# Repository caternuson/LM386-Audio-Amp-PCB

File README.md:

# LM386 Audio Amp PCB
EAGLE files for simple LM386 single channel audio amp with adjustable gain. Also available at [OSH Park](https://oshpark.com/shared_projects/PH3KykbY).

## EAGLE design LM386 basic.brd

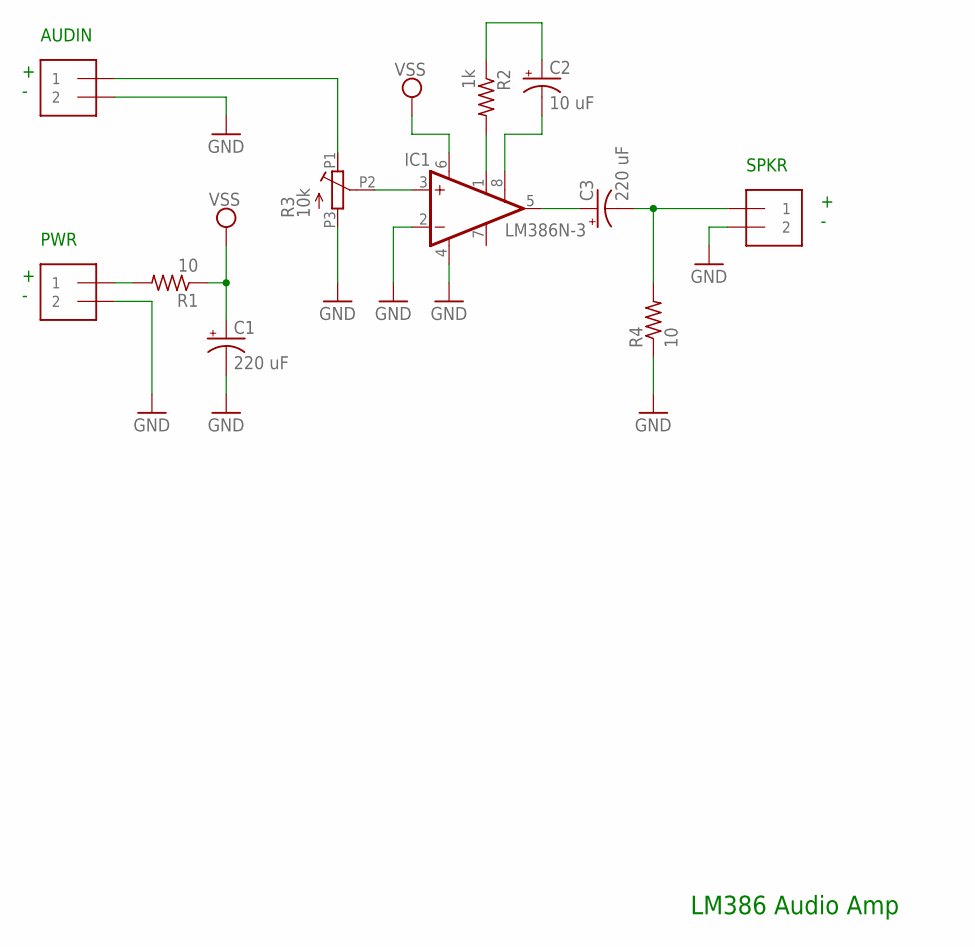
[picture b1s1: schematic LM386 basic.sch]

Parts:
AUDIN: 1X2-3.5MM
C1, C3: 220 uF; E2,5-6
C2: 10 uF; E2-5
IC1: LM386N-3; DIL08
PWR: 1X2-3.5MM
R1, R4: 10; 0309/12
R2: 1k; 0309/12
R3: 10k; POT-THRU-01
SPKR: 1X2-3.5MM

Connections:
GND: AUDIN.2, C1.-, IC1.2 (-IN), IC1.4 (GND), PWR.2, R3.P3 (A), R4.1, SPKR.2
unnamed: AUDIN.1, R3.P1 (E)
unnamed: C3.+, IC1.5 (OUT)
unnamed: IC1.1 (GAIN), R2.2
unnamed: C3.-, R4.2, SPKR.1
unnamed: IC1.3 (+IN), R3.P2 (S)
unnamed: PWR.1, R1.2
unnamed: C2.+, R2.1
unnamed: C2.-, IC1.8 (GAIN)
VSS: C1.+, IC1.6 (VS), R1.1

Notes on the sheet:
LM386 Audio Amp
PWR
AUDIN
SPKR
+ -

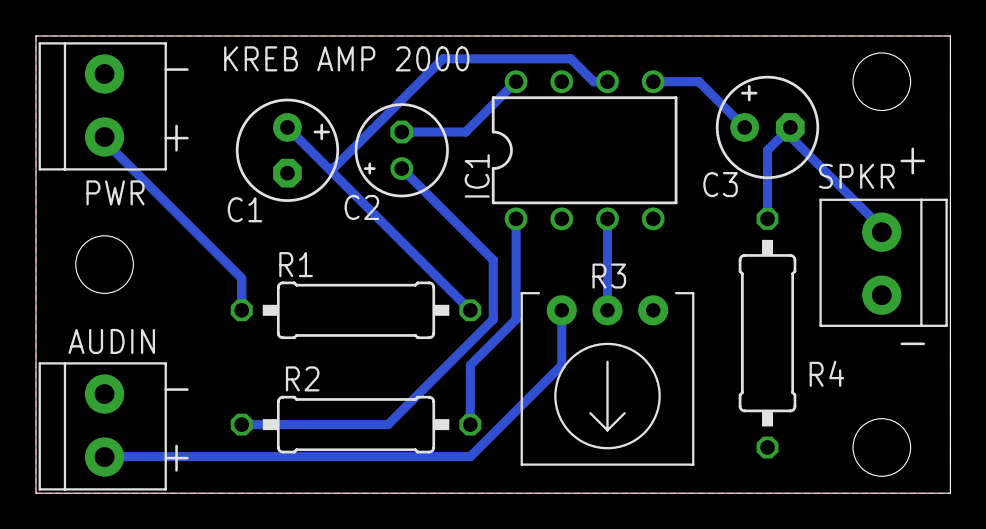
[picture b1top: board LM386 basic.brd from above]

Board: 2 copper layers, 50.8 x 25.4 mm, 11 parts (0 on the bottom side), 10 nets.

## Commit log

2016-07-01 Create LICENSE
2016-07-01 added info to title block
